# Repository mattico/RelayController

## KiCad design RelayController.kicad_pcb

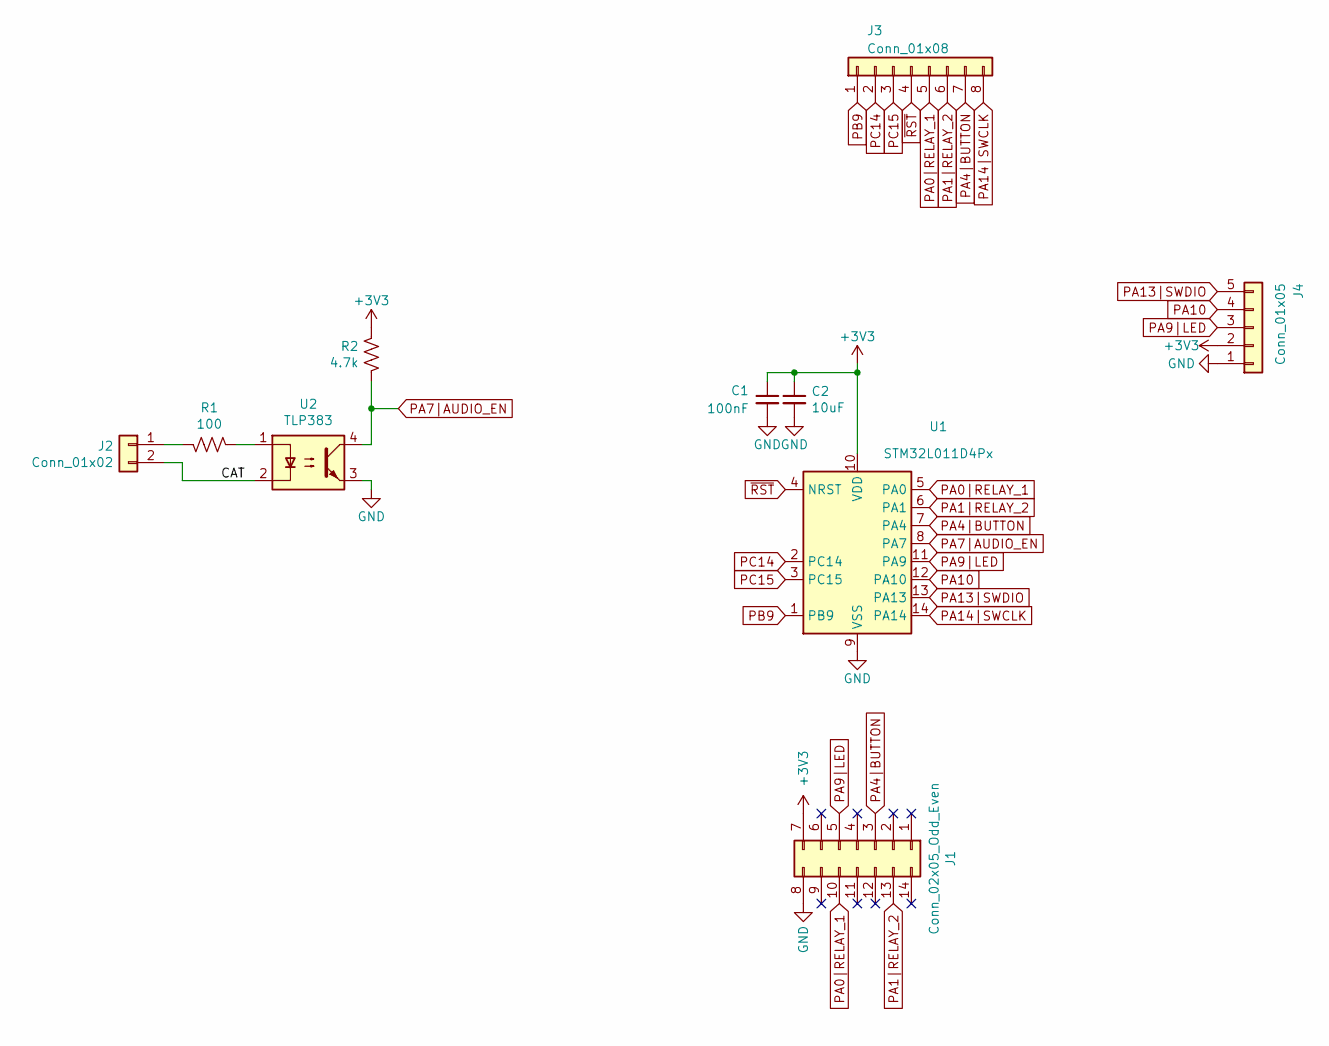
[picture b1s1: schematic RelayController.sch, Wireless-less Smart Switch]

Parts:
C1: 100nF; C_0603_1608Metric_Pad1.05x0.95mm_HandSolder
C2: 10uF; C_0603_1608Metric_Pad1.05x0.95mm_HandSolder
J1: Conn_02x05_Odd_Even; BoardEdgeSolderConnector
J2: Conn_01x02; JST_XH_B02B-XH-AM_1x02_P2.50mm_Vertical
J3: Conn_01x08; PinHeader_1x08_P2.00mm_Vertical
J4: Conn_01x05; PinHeader_1x05_P2.00mm_Vertical
R1: 100; R_0603_1608Metric_Pad1.05x0.95mm_HandSolder
R2: 4.7k; R_0603_1608Metric_Pad1.05x0.95mm_HandSolder
U1: STM32L011D4Px; TSSOP-14_4.4x5mm_P0.65mm
U2: TLP383; SMDIP-4_W9.53mm

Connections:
+3V3: C1.1, C2.1, J1.7, J4.2, R2.2, U1.10 (VDD)
/CAT: J2.2, U2.2
GND: C1.2, C2.2, J1.8, J4.1, U1.9 (VSS), U2.3
unnamed: J2.1, R1.1
unnamed: R1.2, U2.1
PA0|RELAY_1: J1.10, J3.5, U1.5 (PA0)
PA1|RELAY_2: J1.13, J3.6, U1.6 (PA1)
PA4|BUTTON: J1.3, J3.7, U1.7 (PA4)
PA7|AUDIO_EN: R2.1, U1.8 (PA7), U2.4
PA9|LED: J1.5, J4.3, U1.11 (PA9)
PA10: J4.4, U1.12 (PA10)
PA13|SWDIO: J4.5, U1.13 (PA13)
PA14|SWCLK: J3.8, U1.14 (PA14)
PB9: J3.1, U1.1 (PB9)
PC14: J3.2, U1.2 (PC14)
PC15: J3.3, U1.3 (PC15)
~RST: J3.4, U1.4 (NRST)

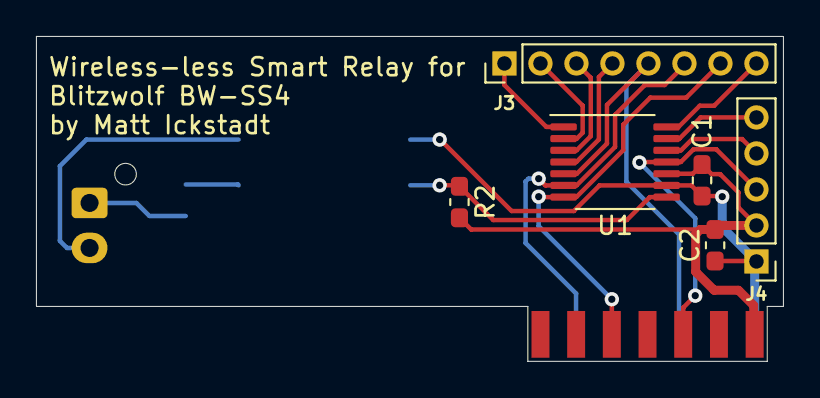
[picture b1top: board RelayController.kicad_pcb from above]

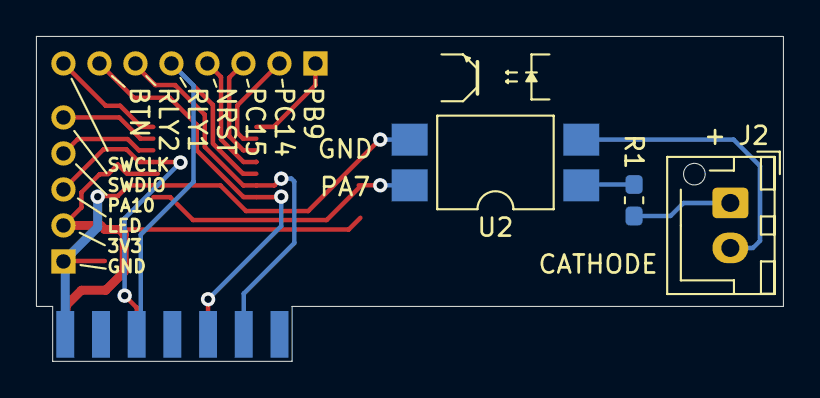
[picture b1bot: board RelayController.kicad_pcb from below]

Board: 2 copper layers, 41.5 x 18.1 mm, 10 parts (3 on the bottom side), 17 nets.

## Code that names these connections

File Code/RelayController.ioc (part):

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PA0-CK_IN.GPIO_Label=RELAY_1
PA0-CK_IN.GPIOParameters=GPIO_Label
Mcu.UserName=STM32L011D4Px
PA9.GPIO_Label=LED
PA9.GPIOParameters=GPIO_Label,GPIO_ModeDefaultOutputPP
RCC.SYSCLKSource=RCC_SYSCLKSOURCE_HSI
PA13.Signal=SYS_SWDIO
PA9.Signal=GPIO_Output
PA1.Signal=GPIO_Output
PA7.GPIO_PuPd=GPIO_PULLUP
RCC.HSE_VALUE=8000000
PA4.GPIO_PuPd=GPIO_PULLUP
board=custom
PA0-CK_IN.Signal=GPIO_Output
PA1.GPIOParameters=GPIO_Label
PA14.Mode=Serial_Wire
PA1.GPIO_Label=RELAY_2
PA4.GPIOParameters=GPIO_PuPd,GPIO_Label
PA13.Mode=Serial_Wire
Mcu.Name=STM32L011D(3-4)Px
PA9.GPIO_ModeDefaultOutputPP=GPIO_MODE_OUTPUT_OD
PA4.Signal=GPIO_Input
RCC.SYSCLKFreq_VALUE=16000000
Mcu.Package=TSSOP14
PA7.GPIO_Label=AUDIO_EN
PA14.Signal=SYS_SWCLK
PA4.GPIO_Label=BUTTON
PA7.GPIOParameters=GPIO_PuPd,GPIO_Label
PA7.Signal=GPIO_Input

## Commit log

2020-09-23 Add license
2020-09-24 Fix LED GPIO state
2020-09-24 Fix bug with button not working after audio disable
2020-11-11 Implement turn-off pop trigger avoidance
